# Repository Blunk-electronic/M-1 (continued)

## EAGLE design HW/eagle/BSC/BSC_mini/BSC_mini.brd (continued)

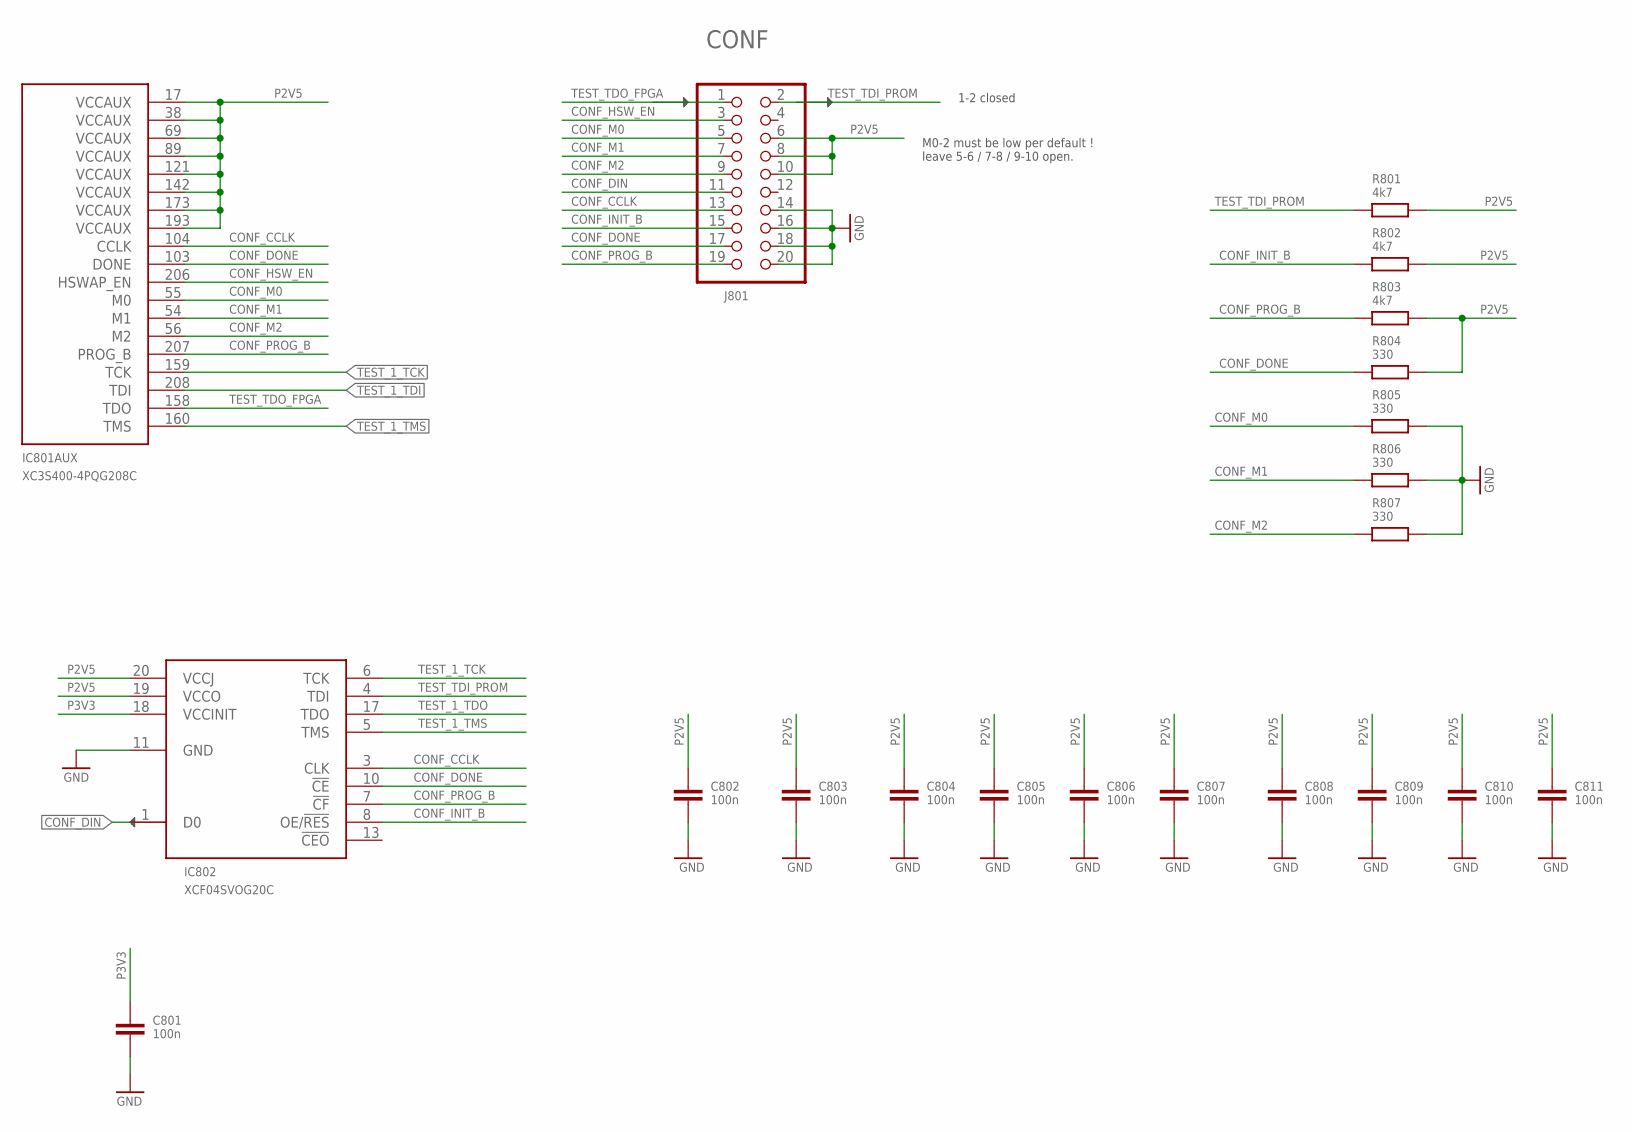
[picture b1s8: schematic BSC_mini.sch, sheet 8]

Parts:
C801, C802, C803, C804, C805, C806, C807, C808, C809, C810, C811: 100n; S_0805; PART_CODE_BEL C_PAC_S_0805_VAL_100n
IC801: XC3S400-4PQG208C; S_PQ208
IC802: XCF04SVOG20C; S_TSSOP20
J801: JUMPER_2X10-T-VERTICAL; T_MALE_2X10_VERTICAL_GRID_2.54MM; PART_CODE_BEL J_PAC_T_MALE_2X10_VERTICAL_PITCH_2mm54
R801, R802, R803: 4k7; S_0805; PART_CODE_BEL R_PAC_S_0805_VAL_4k7
R804, R805, R806, R807: 330; S_0805; PART_CODE_BEL R_PAC_S_0805_VAL_330

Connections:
CONF_CCLK: IC801.104 (CCLK), IC802.3 (CLK), J801.13
CONF_DIN: IC802.1 (D0), J801.11; also elsewhere on the board
CONF_DONE: IC801.103 (DONE), IC802.10 (!CE), J801.17, R804.1
CONF_HSW_EN: IC801.206 (HSWAP_EN), J801.3
CONF_INIT_B: IC802.8 (OE/!RES), J801.15, R802.1; also elsewhere on the board
CONF_M0: IC801.55 (M0), J801.5, R805.1
CONF_M1: IC801.54 (M1), J801.7, R806.1
CONF_M2: IC801.56 (M2), J801.9, R807.1
CONF_PROG_B: IC801.207 (PROG_B), IC802.7 (!CF), J801.19, R803.1
GND: C801.2, C802.2, C803.2, C804.2, C805.2, C806.2, C807.2, C808.2, C809.2, C810.2, C811.2, IC802.11 (GND), J801.14, J801.16, J801.18, J801.20, R805.2, R806.2, R807.2; also elsewhere on the board
P2V5: C802.1, C803.1, C804.1, C805.1, C806.1, C807.1, C808.1, C809.1, C810.1, C811.1, IC801.17 (VCCAUX), IC801.38 (VCCAUX), IC801.69 (VCCAUX), IC801.89 (VCCAUX), IC801.121 (VCCAUX), IC801.142 (VCCAUX), IC801.173 (VCCAUX), IC801.193 (VCCAUX), IC802.19 (VCCO), IC802.20 (VCCJ), J801.6, J801.8, J801.10, R801.2, R802.2, R803.2, R804.2; also elsewhere on the board
P3V3: C801.1, IC802.18 (VCCINIT); also elsewhere on the board
TEST_1_TCK: IC801.159 (TCK), IC802.6 (TCK); also elsewhere on the board
TEST_1_TDI: IC801.208 (TDI); also elsewhere on the board
TEST_1_TDO: IC802.17 (TDO); also elsewhere on the board
TEST_1_TMS: IC801.160 (TMS), IC802.5 (TMS); also elsewhere on the board
TEST_TDI_PROM: IC802.4 (TDI), J801.2, R801.1
TEST_TDO_FPGA: IC801.158 (TDO), J801.1

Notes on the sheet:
M0-2 must be low per default ! leave 5-6 / 7-8 / 9-10 open.
1-2 closed

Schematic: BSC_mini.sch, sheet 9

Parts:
IC801: XC3S400-4PQG208C; S_PQ208

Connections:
CLK_MASTER: IC801.181 (IO_L32N_1/GCLK5); also elsewhere on the board
CLK_SLOW: IC801.154 (IO/VREF_2); also elsewhere on the board
DEBUG_4: IC801.149 (IO_L20N_2); also elsewhere on the board
DEBUG_5: IC801.150 (IO_L19P_2); also elsewhere on the board
DEBUG_6: IC801.152 (IO_L19N_2); also elsewhere on the board
MEM_A0: IC801.122 (IO_L23P_3/VREF_3); also elsewhere on the board
MEM_A1: IC801.123 (IO_L23N_3); also elsewhere on the board
MEM_A2: IC801.124 (IO_L24P_3); also elsewhere on the board
MEM_A3: IC801.125 (IO_L24N_3); also elsewhere on the board
MEM_A4: IC801.126 (IO_L39P_3); also elsewhere on the board
MEM_A5: IC801.128 (IO_L39N_3); also elsewhere on the board
MEM_A6: IC801.130 (IO_L40P_3); also elsewhere on the board
MEM_A7: IC801.131 (IO_L40N_3/VREF_3); also elsewhere on the board
MEM_A8: IC801.132 (IO_L40P_2/VREF_2); also elsewhere on the board
MEM_A9: IC801.133 (IO_L40N_2); also elsewhere on the board
MEM_A10: IC801.135 (IO_L39P_2); also elsewhere on the board
MEM_A11: IC801.137 (IO_L39N_2); also elsewhere on the board
MEM_A12: IC801.138 (IO_L24P_2); also elsewhere on the board
MEM_A13: IC801.139 (IO_L24N_2); also elsewhere on the board
MEM_A14: IC801.140 (IO_L23P_2); also elsewhere on the board
MEM_A15: IC801.141 (IO_L23N_2/VREF_2); also elsewhere on the board
MEM_A16: IC801.143 (IO_L22P_2); also elsewhere on the board
MEM_A17: IC801.144 (IO_L22N_2); also elsewhere on the board
MEM_A18: IC801.146 (IO_L21P_2); also elsewhere on the board
MEM_D0: IC801.106 (IO_L01P_3/VRN_3); also elsewhere on the board
MEM_D1: IC801.107 (IO_L01N_3/VRP_3); also elsewhere on the board
MEM_D2: IC801.108 (IO_L17P_3/VREF_3); also elsewhere on the board
MEM_D3: IC801.109 (IO_L17N_3); also elsewhere on the board
MEM_D4: IC801.111 (IO_L19P_3); also elsewhere on the board
MEM_D5: IC801.113 (IO_L19N_3); also elsewhere on the board
MEM_D6: IC801.114 (IO_L20P_3); also elsewhere on the board
MEM_D7: IC801.115 (IO_L20N_3); also elsewhere on the board
P3V3: IC801.110 (VCCO_3), IC801.127 (VCCO_3), IC801.136 (VCCO_2), IC801.153 (VCCO_2), IC801.164 (VCCO_1), IC801.177 (VCCO_1), IC801.188 (VCCO_0), IC801.201 (VCCO_0); also elsewhere on the board
RAM_IN_CS_N: IC801.117 (IO_L21N_3); also elsewhere on the board
RAM_OE_N: IC801.120 (IO_L22N_3); also elsewhere on the board
RAM_OUT_CS_1_N: IC801.116 (IO_L21P_3); also elsewhere on the board
RAM_OUT_CS_2_N: IC801.147 (IO_L21N_2); also elsewhere on the board
RAM_WE_N: IC801.119 (IO_L22P_3); also elsewhere on the board
ROM_CS_N: IC801.148 (IO_L20P_2); also elsewhere on the board
ST_1_OUT: IC801.166 (IO_L10N_1/VREF_1); also elsewhere on the board
ST_2_OUT: IC801.165 (IO_L10P_1); also elsewhere on the board
SYS_RESET_N: IC801.182 (IO); also elsewhere on the board
UART_CTS: IC801.199 (IO_L25N_0); also elsewhere on the board
UART_RTS: IC801.198 (IO_L25P_0); also elsewhere on the board
UART_RXD: IC801.203 (IO_L01P_0/VRN_0); also elsewhere on the board
UART_TXD: IC801.200 (IO/VREF_0); also elsewhere on the board

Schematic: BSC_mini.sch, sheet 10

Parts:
IC801: XC3S400-4PQG208C; S_PQ208
TP1001, TP1002, TP1003: TEST_POINT_T_SMALL; T_TEST_POINT_SMALL

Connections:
ACL_OUT: IC801.2 (IO_L01P_7/VRN_7); also elsewhere on the board
CONF_DIN: IC801.92 (IO_L27N_4/DIN/D0); also elsewhere on the board
CONF_DOUT: IC801.81 (IO_L31P_4/DOUT/BUSY), TP1002.1
CONF_INIT_B: IC801.83 (IO_L31N_4/INIT_B); also elsewhere on the board
CTRL_IN_START_N: IC801.35 (IO_L24N_6/VREF_6); also elsewhere on the board
CTRL_IN_STOP_N: IC801.34 (IO_L24P_6); also elsewhere on the board
CTRL_OUT_FAIL: IC801.58 (IO_L01N_5/RDWR_B); also elsewhere on the board
CTRL_OUT_PASS: IC801.57 (IO_L01P_5/CS_B); also elsewhere on the board
DBG_3: IC801.43 (IO_L21N_6); also elsewhere on the board
DBG_4: IC801.96 (IO/VREF_4); also elsewhere on the board
DBG_5: IC801.40 (IO_L22N_6); also elsewhere on the board
DBG_6: IC801.39 (IO_L22P_6); also elsewhere on the board
DBG_80: IC801.80 (IO_L32N_4/GCLK1), TP1003.1
DBG_81: IC801.97 (IO), TP1001.1
DCL_OUT: IC801.3 (IO_L01N_7/VRP_7); also elsewhere on the board
DEBUG_0: IC801.61 (IO_L10P_5/VRN_5); also elsewhere on the board
DEBUG_1: IC801.33 (IO_L39N_6); also elsewhere on the board
DEBUG_2: IC801.44 (IO_L20P_6); also elsewhere on the board
DEBUG_3: IC801.37 (IO_L23N_6); also elsewhere on the board
I2C_SCL: IC801.51 (IO_L01P_6/VRN_6); also elsewhere on the board
I2C_SDA: IC801.52 (IO_L01N_6/VRP_6); also elsewhere on the board
OBI_1: IC801.36 (IO_L23P_6); also elsewhere on the board
OBI_2: IC801.4 (IO_L16P_7/VREF_7); also elsewhere on the board
OBI_3: IC801.10 (IO_L20P_7); also elsewhere on the board
OBI_4: IC801.11 (IO_L20N_7); also elsewhere on the board
OBI_5: IC801.12 (IO_L21P_7); also elsewhere on the board
OBI_6: IC801.29 (IO_L40N_6); also elsewhere on the board
OBI_7: IC801.50 (IO/VREF_6); also elsewhere on the board
OBI_8: IC801.48 (IO_L19N_6); also elsewhere on the board
OBI_9: IC801.46 (IO_L19P_6); also elsewhere on the board
OBI_10: IC801.45 (IO_L20N_6); also elsewhere on the board
P2V5: IC801.84 (VCCO_4), IC801.98 (VCCO_4); also elsewhere on the board
P3V3: IC801.6 (VCCO_7), IC801.23 (VCCO_7), IC801.32 (VCCO_6), IC801.49 (VCCO_6), IC801.60 (VCCO_5), IC801.73 (VCCO_5); also elsewhere on the board
SP_1_FAIL_FPGA: IC801.63 (IO); also elsewhere on the board
SP_1_TCK_FPGA: IC801.76 (IO_L32P_5/GCLK2); also elsewhere on the board
SP_1_TDI_FPGA: IC801.78 (IO/VREF_5); also elsewhere on the board
SP_1_TDO_FPGA: IC801.68 (IO_L28N_5/D6); also elsewhere on the board
SP_1_TMS_FPGA: IC801.74 (IO_L31N_5/D4); also elsewhere on the board
SP_1_TRST_FPGA: IC801.65 (IO_L27N_5/VREF_5); also elsewhere on the board
SP_2_FAIL_FPGA: IC801.62 (IO_L10N_5/VRP_5); also elsewhere on the board
SP_2_TCK_FPGA: IC801.77 (IO_L32N_5/GCLK3); also elsewhere on the board
SP_2_TDI_FPGA: IC801.71 (IO); also elsewhere on the board
SP_2_TDO_FPGA: IC801.67 (IO_L28P_5/D7); also elsewhere on the board
SP_2_TMS_FPGA: IC801.72 (IO_L31P_5/D5); also elsewhere on the board
SP_2_TRST_FPGA: IC801.64 (IO_L27P_5); also elsewhere on the board

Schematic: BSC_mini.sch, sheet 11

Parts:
C1101, C1102, C1103, C1104, C1105, C1106, C1107, C1108, C1109, C1110, C1111, C1112, C1113, C1114, C1115, C1116, C1117, C1118, C1119, C1120: 100n; S_0805; PART_CODE_BEL C_PAC_S_0805_VAL_100n
IC801: XC3S400-4PQG208C; S_PQ208
IC1101: 50MHz; S_XO91; PART_CODE_BEL IC_PAC_S_XO91_7x5mm_VAL_50MHz
TP1101: TEST_POINT_T_SMALL; T_TEST_POINT_SMALL

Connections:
CLK_MASTER: IC1101.3 (FO), TP1101.1; also elsewhere on the board
GND: C1101.2, C1102.2, C1103.2, C1104.2, C1105.2, C1106.2, C1107.2, C1108.2, C1109.2, C1110.2, C1111.2, C1112.2, C1113.2, C1114.2, C1115.2, C1116.2, C1117.2, C1118.2, C1119.2, C1120.2, IC801.1 (GND), IC801.8 (GND), IC801.14 (GND), IC801.25 (GND), IC801.30 (GND), IC801.41 (GND), IC801.47 (GND), IC801.53 (GND), IC801.59 (GND), IC801.66 (GND), IC801.75 (GND), IC801.82 (GND), IC801.91 (GND), IC801.99 (GND), IC801.105 (GND), IC801.112 (GND), IC801.118 (GND), IC801.129 (GND), IC801.134 (GND), IC801.145 (GND), IC801.151 (GND), IC801.157 (GND), IC801.163 (GND), IC801.170 (GND), IC801.179 (GND), IC801.186 (GND), IC801.195 (GND), IC801.202 (GND), IC1101.2 (GND); also elsewhere on the board
P1V2: C1117.1, C1118.1, C1119.1, C1120.1, IC801.70 (VCCINT), IC801.88 (VCCINT), IC801.174 (VCCINT), IC801.192 (VCCINT); also elsewhere on the board
P2V5: C1114.1; also elsewhere on the board
P3V3: C1101.1, C1102.1, C1103.1, C1104.1, C1105.1, C1106.1, C1107.1, C1108.1, C1109.1, C1110.1, C1111.1, C1112.1, C1113.1, C1115.1, C1116.1, IC1101.4 (VCC); also elsewhere on the board

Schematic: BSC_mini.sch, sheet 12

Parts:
IC1201: XC2C384-10TQG144C; S_TQFP144; PART_CODE_BEL IC_PAC_S_TQFP144_VAL_XC2C384-10TQG144C
J1201: JUMPER_1X2-T-VERTICAL_GRID_2.54MM; T_MALE_2X1_VERTICAL_PITCH_2MM54
R1201, R1202: 330; S_0805; PART_CODE_BEL R_PAC_S_0805_VAL_330
RN1201: 10k; S_1206_4X; PART_CODE_BEL RN_PAC_S_1206_4X_VAL_10k
X1201, X1202: MALE_2X5-T-VERTICAL_2MM54; T_MALE_2X5_VERTICAL_PITCH_2MM54

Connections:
GND: R1201.1, R1202.1, X1201.2, X1201.4, X1201.6, X1201.8, X1202.2, X1202.4, X1202.6, X1202.8; also elsewhere on the board
P3V3: J1201.1; also elsewhere on the board
TEST_2_TCK: IC1201.67 (TCK), R1201.2, X1201.1, X1202.1
TEST_2_TDI: IC1201.63 (TDI), RN1201.2 (1), X1201.7, X1202.7
TEST_2_TDO: IC1201.122 (TDO), RN1201.3 (1), X1201.5, X1202.5
TEST_2_TMS: IC1201.65 (TMS), R1202.2, X1201.3, X1202.3
TEST_2_VREF: J1201.2, RN1201.6 (2), RN1201.7 (2), X1201.10, X1202.10

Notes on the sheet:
NOTE: close for in-system-programming

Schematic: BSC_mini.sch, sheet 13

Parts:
C1301, C1302: 100n; S_0805; PART_CODE_BEL C_PAC_S_0805_VAL_100n
IC1301, IC1302: MAX517ACSA+; S_SO8; PART_CODE_BEL IC_PAC_S_SO8_VAL_MAX517ACSA+
R1301, R1302: 330; S_0805; PART_CODE_BEL R_PAC_S_0805_VAL_330

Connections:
GND: C1301.2, C1302.2, IC1301.2 (GND), IC1301.5 (A1), IC1301.6 (A0), IC1302.2 (GND), IC1302.5 (A1); also elsewhere on the board
I2C_SCL: IC1301.3 (SCL), IC1302.3 (SCL), R1301.1; also elsewhere on the board
I2C_SDA: IC1301.4 (SDA), IC1302.4 (SDA), R1302.1; also elsewhere on the board
P3V3: IC1301.8 (VREF0), IC1302.8 (VREF0), R1301.2, R1302.2; also elsewhere on the board
P5V: C1301.1, C1302.1, IC1301.7 (VCC), IC1302.6 (A0), IC1302.7 (VCC); also elsewhere on the board
SP_1_TDI_VREF: IC1301.1 (OUT0); also elsewhere on the board
SP_2_TDI_VREF: IC1302.1 (OUT0); also elsewhere on the board

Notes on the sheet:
I²C write addr 58h
I²C write addr 5Ah

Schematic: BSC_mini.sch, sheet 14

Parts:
C1401: 100n; S_0805; PART_CODE_BEL C_PAC_S_0805_VAL_100n
D1401, D1402: BAT54S; S_SOT23; PART_CODE_BEL D_PAC_S_SOT23_VAL_BAT54S
IC1401: MAX962ESA+; S_SO8; PART_CODE_BEL IC_PAC_S_SO8_VAL_MAX962ESA+
R1401, R1403: 8k2; S_0805; PART_CODE_BEL R_PAC_S_0805_VAL_8k2
R1402, R1404: 2k7; S_0805; PART_CODE_BEL R_PAC_S_0805_VAL_2k7
TP1401, TP1402, TP1403, TP1404, TP1405, TP1406: TEST_POINT_T_SMALL; T_TEST_POINT_SMALL

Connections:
GND: C1401.1, D1401.1 (A2), D1402.1 (A2), IC1401.5 (V-), R1402.1, R1404.1; also elsewhere on the board
P3V3: C1401.2, D1401.2 (K1), D1402.2 (K1), IC1401.8 (V+), R1401.2, R1403.2; also elsewhere on the board
SP_1_TDI: D1401.3 (A1K2), IC1401.3 (+IN), TP1401.1; also elsewhere on the board
SP_1_TDI_COMP: IC1401.6 (OUT), TP1405.1; also elsewhere on the board
SP_1_TDI_VREF: IC1401.4 (-IN), R1401.1, R1402.2, TP1402.1; also elsewhere on the board
SP_2_TDI: D1402.3 (A1K2), IC1401.1 (+IN), TP1403.1; also elsewhere on the board
SP_2_TDI_COMP: IC1401.7 (OUT), TP1406.1; also elsewhere on the board
SP_2_TDI_VREF: IC1401.2 (-IN), R1403.1, R1404.2, TP1404.1; also elsewhere on the board

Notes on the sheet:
fixed reference voltage for comparators NOT FITTED
0.82V

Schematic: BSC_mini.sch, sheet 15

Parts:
IC1201: XC2C384-10TQG144C; S_TQFP144; PART_CODE_BEL IC_PAC_S_TQFP144_VAL_XC2C384-10TQG144C

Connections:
DEBUG_10: IC1201.143 (B2_FB1_MC3(GSR)); also elsewhere on the board
DEBUG_11: IC1201.142 (B2_FB1_MC4); also elsewhere on the board
DEBUG_12: IC1201.34 (B1_FB7_MC4); also elsewhere on the board
DEBUG_13: IC1201.33 (B1_FB7_MC5); also elsewhere on the board
DEBUG_14: IC1201.38 (B1_FB8_MC2(GCK2)); also elsewhere on the board
DEBUG_15: IC1201.39 (B1_FB8_MC5(DGE)); also elsewhere on the board
DEBUG_16: IC1201.40 (B1_FB8_MC13); also elsewhere on the board
DEBUG_17: IC1201.41 (B1_FB8_MC14); also elsewhere on the board
DEBUG_18: IC1201.42 (B1_FB8_MC15); also elsewhere on the board
DISP_1_SEG_A: IC1201.7 (B2_FB2_MC16); also elsewhere on the board
DISP_1_SEG_B: IC1201.6 (B2_FB2_MC15(GTS1)); also elsewhere on the board
DISP_1_SEG_C: IC1201.4 (B2_FB2_MC4); also elsewhere on the board
DISP_1_SEG_D: IC1201.2 (B2_FB2_MC1(GTS2)); also elsewhere on the board
DISP_1_SEG_E: IC1201.3 (B2_FB2_MC3(GTS3)); also elsewhere on the board
DISP_1_SEG_F: IC1201.5 (B2_FB2_MC5(GTS0)); also elsewhere on the board
DISP_1_SEG_G: IC1201.23 (B1_FB11_MC2); also elsewhere on the board
DISP_1_SEG_H: IC1201.25 (B1_FB9_MC16); also elsewhere on the board
DISP_2_SEG_A: IC1201.26 (B1_FB9_MC15); also elsewhere on the board
DISP_2_SEG_B: IC1201.28 (B1_FB9_MC2); also elsewhere on the board
DISP_2_SEG_C: IC1201.24 (B1_FB11_MC1); also elsewhere on the board
DISP_2_SEG_D: IC1201.50 (B1_FB10_MC16); also elsewhere on the board
DISP_2_SEG_E: IC1201.49 (B1_FB10_MC15); also elsewhere on the board
DISP_2_SEG_F: IC1201.44 (B1_FB10_MC1); also elsewhere on the board
DISP_2_SEG_G: IC1201.46 (B1_FB10_MC4); also elsewhere on the board
DISP_2_SEG_H: IC1201.48 (B1_FB10_MC14); also elsewhere on the board
I2C_SCL: IC1201.32 (B1_FB7_MC12(GCK1)); also elsewhere on the board
I2C_SDA: IC1201.31 (B1_FB7_MC14); also elsewhere on the board
OBI_1: IC1201.139 (B2_FB1_MC13); also elsewhere on the board
OBI_2: IC1201.52 (B1_FB12_MC2); also elsewhere on the board
OBI_3: IC1201.51 (B1_FB12_MC1); also elsewhere on the board
OBI_4: IC1201.45 (B1_FB10_MC2); also elsewhere on the board
OBI_5: IC1201.43 (B1_FB8_MC16); also elsewhere on the board
OBI_6: IC1201.140 (B2_FB1_MC12); also elsewhere on the board
OBI_7: IC1201.22 (B1_FB11_MC3); also elsewhere on the board
OBI_8: IC1201.21 (B1_FB11_MC4); also elsewhere on the board
OBI_9: IC1201.20 (B1_FB11_MC5); also elsewhere on the board
OBI_10: IC1201.19 (B1_FB11_MC12); also elsewhere on the board
SP_1_DIO_1_ADJ: IC1201.102 (B4_FB16_MC3); also elsewhere on the board
SP_1_DIO_1_P3V3: IC1201.135 (B2_FB3_MC12); also elsewhere on the board
SP_1_DIO_2_ADJ: IC1201.105 (B4_FB14_MC5); also elsewhere on the board
SP_1_DIO_2_P3V3: IC1201.136 (B2_FB3_MC5); also elsewhere on the board
SP_1_TCK: IC1201.104 (B4_FB14_MC13); also elsewhere on the board
SP_1_TCK_FPGA: IC1201.9 (B2_FB4_MC1); also elsewhere on the board
SP_1_TDI_COMP: IC1201.137 (B2_FB3_MC4); also elsewhere on the board
SP_1_TDI_FPGA: IC1201.17 (B2_FB6_MC14); also elsewhere on the board
SP_1_TDO: IC1201.107 (B4_FB14_MC3); also elsewhere on the board
SP_1_TDO_FPGA: IC1201.11 (B2_FB4_MC3); also elsewhere on the board
SP_1_TMS: IC1201.103 (B4_FB16_MC1); also elsewhere on the board
SP_1_TMS_FPGA: IC1201.10 (B2_FB4_MC2); also elsewhere on the board
SP_1_TRST_FPGA: IC1201.12 (B2_FB4_MC4); also elsewhere on the board
SP_1_TRST_N: IC1201.106 (B4_FB14_MC4); also elsewhere on the board
SP_1_VCC_P1V5_SET: IC1201.134 (B2_FB3_MC16); also elsewhere on the board
SP_1_VCC_P1V8_SET: IC1201.133 (B2_FB5_MC2); also elsewhere on the board
SP_1_VCC_P2V5_SET: IC1201.132 (B2_FB5_MC3); also elsewhere on the board
SP_2_DIO_1_ADJ: IC1201.87 (B3_FB23_MC5); also elsewhere on the board
SP_2_DIO_1_P3V3: IC1201.53 (B1_FB12_MC3); also elsewhere on the board
SP_2_DIO_2_ADJ: IC1201.85 (B3_FB23_MC3); also elsewhere on the board
SP_2_DIO_2_P3V3: IC1201.54 (B1_FB12_MC5); also elsewhere on the board
SP_2_TCK: IC1201.92 (B3_FB23_MC14); also elsewhere on the board
SP_2_TCK_FPGA: IC1201.13 (B2_FB6_MC2); also elsewhere on the board
SP_2_TDI_COMP: IC1201.138 (B2_FB3_MC3); also elsewhere on the board
SP_2_TDI_FPGA: IC1201.18 (B2_FB6_MC16); also elsewhere on the board
SP_2_TDO: IC1201.88 (B3_FB23_MC12); also elsewhere on the board
SP_2_TDO_FPGA: IC1201.15 (B2_FB6_MC4); also elsewhere on the board
SP_2_TMS: IC1201.91 (B3_FB23_MC13); also elsewhere on the board
SP_2_TMS_FPGA: IC1201.14 (B2_FB6_MC3); also elsewhere on the board
SP_2_TRST_FPGA: IC1201.16 (B2_FB6_MC13); also elsewhere on the board
SP_2_TRST_N: IC1201.86 (B3_FB23_MC4); also elsewhere on the board
SP_2_VCC_P1V5_SET: IC1201.131 (B2_FB5_MC13); also elsewhere on the board
SP_2_VCC_P1V8_SET: IC1201.130 (B2_FB5_MC15); also elsewhere on the board
SP_2_VCC_P2V5_SET: IC1201.129 (B2_FB5_MC16); also elsewhere on the board
SYS_RESET_N: IC1201.35 (B1_FB7_MC1(CDRST)); also elsewhere on the board

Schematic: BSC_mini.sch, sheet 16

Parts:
C1601, C1602, C1603, C1604, C1605, C1606, C1607, C1608, C1609, C1610, C1611: 100n; S_0805; PART_CODE_BEL C_PAC_S_0805_VAL_100n
IC1201: XC2C384-10TQG144C; S_TQFP144; PART_CODE_BEL IC_PAC_S_TQFP144_VAL_XC2C384-10TQG144C

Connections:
GND: C1601.2, C1602.2, C1603.2, C1604.2, C1605.2, C1606.2, C1607.2, C1608.2, C1609.2, C1610.2, C1611.2, IC1201.29 (GND), IC1201.36 (GND), IC1201.47 (GND), IC1201.62 (GND), IC1201.72 (GND), IC1201.89 (GND), IC1201.90 (GND), IC1201.99 (GND), IC1201.108 (GND), IC1201.123 (GND), IC1201.144 (GND); also elsewhere on the board
P1V8: C1603.1, C1606.1, C1609.1, IC1201.1 (VCC), IC1201.37 (VCC), IC1201.84 (VCC); also elsewhere on the board
P3V3: C1602.1, C1605.1, C1608.1, C1611.1, IC1201.8 (VAUX), IC1201.27 (VCC_IO), IC1201.55 (VCC_IO), IC1201.141 (VCC_IO); also elsewhere on the board
SP_1_VCC: C1601.1, C1604.1, IC1201.109 (VCC_IO), IC1201.127 (VCC_IO); also elsewhere on the board
SP_2_VCC: C1607.1, C1610.1, IC1201.73 (VCC_IO), IC1201.93 (VCC_IO); also elsewhere on the board

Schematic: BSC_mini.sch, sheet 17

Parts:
LED1701, LED1702: green; S_0805; PART_CODE_BEL LED_PAC_S_0805_VAL_green
LED1703, LED1704: yellow; S_0805; PART_CODE_BEL LED_PAC_S_0805_VAL_yellow
LED1705, LED1708: blue; S_0805; PART_CODE_BEL LED_PAC_S_0805_VAL_blue
LED1706, LED1707: red; S_0805; PART_CODE_BEL LED_PAC_S_0805_VAL_red
R1701, R1702: 160; S_0805; PART_CODE_BEL R_PAC_S_0805_VAL_160
R1703, R1704: 470; S_0805; PART_CODE_BEL R_PAC_S_0805_VAL_470
R1705, R1708: 330; S_0805; PART_CODE_BEL R_PAC_S_0805_VAL_330
R1706, R1707: 750; S_0805; PART_CODE_BEL R_PAC_S_0805_VAL_750
TP1701: TEST_POINT_T_SMALL; T_TEST_POINT_SMALL
X1701, X1702: MALE_2X20-T-VERTICAL; T_MALE_2X20_VERTICAL_GRID_2.54MM

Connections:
ACL_RC: X1702.40; also elsewhere on the board
CLK_SLOW: X1701.16; also elsewhere on the board
CTRL_IN_START: X1701.34; also elsewhere on the board
CTRL_IN_STOP: X1701.36; also elsewhere on the board
CTRL_OUT_FAIL: X1701.32; also elsewhere on the board
CTRL_OUT_PASS: X1701.30; also elsewhere on the board
DBG_3: X1702.8; also elsewhere on the board
DBG_4: X1702.10; also elsewhere on the board
DBG_5: X1702.12; also elsewhere on the board
DBG_6: X1702.14; also elsewhere on the board
DBG_10_LED: LED1702.C, R1702.2
DBG_11_LED: LED1704.C, R1704.2
DBG_12_LED: LED1706.C, R1706.2
DBG_13_LED: LED1708.C, R1708.2
DEBUG_0: R1701.1, X1702.2; also elsewhere on the board
DEBUG_1: R1703.1, X1702.4; also elsewhere on the board
DEBUG_2: R1705.1, X1702.6; also elsewhere on the board
DEBUG_3: X1702.16; also elsewhere on the board
DEBUG_10: X1702.32; also elsewhere on the board
DEBUG_11: TP1701.1, X1701.14; also elsewhere on the board
DEBUG_12: X1702.28; also elsewhere on the board
DEBUG_13: X1702.30; also elsewhere on the board
DEBUG_14: X1702.26; also elsewhere on the board
DEBUG_15: R1708.1, X1702.24; also elsewhere on the board
DEBUG_16: R1706.1, X1702.22; also elsewhere on the board
DEBUG_17: R1704.1, X1702.20; also elsewhere on the board
DEBUG_18: R1702.1, X1702.18; also elsewhere on the board
DGB_0_LED: LED1701.C, R1701.2
DGB_1_LED: LED1703.C, R1703.2
DGB_2_LED: LED1705.C, R1705.2
GND: X1701.1, X1701.3, X1701.5, X1701.7, X1701.9, X1701.11, X1701.13, X1701.15, X1701.17, X1701.19, X1701.21, X1701.23, X1701.25, X1701.27, X1701.29, X1701.31, X1701.33, X1701.35, X1701.37, X1701.39, X1702.1, X1702.3, X1702.5, X1702.7, X1702.9, X1702.11, X1702.13, X1702.15, X1702.17, X1702.19, X1702.21, X1702.23, X1702.25, X1702.27, X1702.29, X1702.31, X1702.33, X1702.35, X1702.37, X1702.39; also elsewhere on the board
I2C_SCL: X1701.28; also elsewhere on the board
I2C_SDA: X1701.26; also elsewhere on the board
P3V3: LED1701.A, LED1702.A, LED1703.A, LED1704.A, LED1705.A, LED1706.A, LED1707.A, LED1708.A; also elsewhere on the board
RAM_WE_N: X1702.34; also elsewhere on the board
RESET_SWITCH_N: X1701.40; also elsewhere on the board
SP_1_TDI_VREF: X1701.2; also elsewhere on the board
SP_2_TDI_VREF: X1701.4; also elsewhere on the board
ST_1_IN: X1701.18; also elsewhere on the board
ST_1_OUT: X1701.22; also elsewhere on the board
ST_2_IN: X1701.20; also elsewhere on the board
ST_2_OUT: X1701.24; also elsewhere on the board
SYS_RESET_LED: LED1707.C, R1707.2
SYS_RESET_N: R1707.1, X1701.38; also elsewhere on the board

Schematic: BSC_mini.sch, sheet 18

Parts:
C1801, C1802, C1803: 100n; S_0805; PART_CODE_BEL C_PAC_S_0805_VAL_100n
FD1801, FD1802: FIDUCIAL_CROSSHAIR; CROSSHAIR
H1801, H1802, H1803, H1804: HOLE_4.1_PAD; 4.1_PAD
IC1801: 4093N; T_NDIP14
LED1801: green; S_0805; PART_CODE_BEL LED_PAC_S_0805_VAL_green
LED1802: red; S_0805; PART_CODE_BEL LED_PAC_S_0805_VAL_red
R1801: 160; S_0805; PART_CODE_BEL R_PAC_S_0805_VAL_160
R1802: 750; S_0805; PART_CODE_BEL R_PAC_S_0805_VAL_750
R1803, R1804: 1M; S_0805; PART_CODE_BEL R_PAC_S_0805_VAL_1M
RN1801: 100; T_SIL8; PART_CODE_BEL RN_PAC_T_SIL8_VAL_100
S1801, S1802: PUSH_BUTTON_T_6X6MM; T_PUSH_BUTTON_6X6; PART_CODE_BEL S_PAC_T_PUSH_BUTTON_6X6mm
TP1801, TP1802: TEST_POINT_T_SMALL; T_TEST_POINT_SMALL

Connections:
CTRL_IN_START: C1802.1, IC1801.8 (I0), IC1801.9 (I1), R1804.1, S1802.2 (B1), S1802.4 (B1); also elsewhere on the board
CTRL_IN_START_N: IC1801.10 (O); also elsewhere on the board
CTRL_IN_STOP: C1801.1, IC1801.12 (I0), IC1801.13 (I1), R1803.1, S1801.2 (B1), S1801.4 (B1); also elsewhere on the board
CTRL_IN_STOP_N: IC1801.11 (O); also elsewhere on the board
CTRL_OUT_FAIL: R1802.1; also elsewhere on the board
CTRL_OUT_FAIL_LED: LED1802.A, R1802.2
CTRL_OUT_PASS: R1801.1; also elsewhere on the board
CTRL_OUT_PASS_LED: LED1801.A, R1801.2
GND: C1803.2, H1801.H1, H1802.H1, H1803.H1, H1804.H1, IC1801.7 (GND), LED1801.C, LED1802.C, R1803.2, R1804.2, RN1801.1, RN1801.3 (1), RN1801.5 (1), RN1801.7 (1); also elsewhere on the board
P3V3: C1801.2, C1802.2, C1803.1, IC1801.14 (VCC), S1801.1 (A1), S1801.3 (A1), S1802.1 (A1), S1802.3 (A1); also elsewhere on the board
RSV_ST_IN_1: IC1801.1 (I0), RN1801.2
RSV_ST_IN_2: IC1801.2 (I1), RN1801.4 (2)
RSV_ST_IN_3: IC1801.5 (I0), RN1801.6 (2)
RSV_ST_IN_4: IC1801.6 (I1), RN1801.8 (2)
RSV_ST_OUT_1: IC1801.3 (O), TP1801.1
RSV_ST_OUT_2: IC1801.4 (O), TP1802.1

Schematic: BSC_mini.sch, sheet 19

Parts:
DIS1901: VQE14; T_VQEXX_2DIGIT; PART_CODE_BEL DIS_PAC_T_VQExx_2DIGIT_VAL_VQE14
J1901, J1902, J1903, J1904: SOLDER_JUMPER-N; S_SOLDER_JUMPER_NARROW
LED1901: yellow; S_0805; PART_CODE_BEL LED_PAC_S_0805_VAL_yellow
LED1902: blue; S_0805; PART_CODE_BEL LED_PAC_S_0805_VAL_blue
R1901, R1903: 100k; S_0805; PART_CODE_BEL R_PAC_S_0805_VAL_100k
R1902: 470; S_0805; PART_CODE_BEL R_PAC_S_0805_VAL_470
R1904: 330; S_0805; PART_CODE_BEL R_PAC_S_0805_VAL_330
RN1901, RN1902, RN1903, RN1904: 100; T_SIL8; PART_CODE_BEL RN_PAC_T_SIL8_VAL_100
T1901, T1902: DMG3420U; S_SOT23; PART_CODE_BEL T_PAC_S_SOT23_VAL_DMG3420U
TP1901, TP1902, TP1903, TP1904: TEST_POINT_T_SMALL; T_TEST_POINT_SMALL

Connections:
DISP_1_COM: DIS1901.4 (COM1), J1901.2, J1902.2
DISP_1_SEG_A: RN1901.1; also elsewhere on the board
DISP_1_SEG_A_R: DIS1901.16 (A1), RN1901.2
DISP_1_SEG_B: RN1901.3 (1); also elsewhere on the board
DISP_1_SEG_B_R: DIS1901.14 (B1), RN1901.4 (2)
DISP_1_SEG_C: RN1901.5 (1); also elsewhere on the board
DISP_1_SEG_C_R: DIS1901.1 (C1), RN1901.6 (2)
DISP_1_SEG_D: RN1901.7 (1); also elsewhere on the board
DISP_1_SEG_D_R: DIS1901.3 (D1), RN1901.8 (2)
DISP_1_SEG_E: RN1902.1; also elsewhere on the board
DISP_1_SEG_E_R: DIS1901.2 (E1), RN1902.2
DISP_1_SEG_F: RN1902.3 (1); also elsewhere on the board
DISP_1_SEG_F_R: DIS1901.15 (F1), RN1902.4 (2)
DISP_1_SEG_G: RN1902.5 (1); also elsewhere on the board
DISP_1_SEG_G_R: DIS1901.17 (G1), RN1902.6 (2)
DISP_1_SEG_H: RN1902.7 (1); also elsewhere on the board
DISP_1_SEG_H_R: DIS1901.18 (DP1), RN1902.8 (2)
DISP_2_COM: DIS1901.5 (COM2), J1903.1, J1904.1
DISP_2_SEG_A: RN1903.2; also elsewhere on the board
DISP_2_SEG_A_R: DIS1901.11 (A2), RN1903.1
DISP_2_SEG_B: RN1903.4 (2); also elsewhere on the board
DISP_2_SEG_B_R: DIS1901.13 (B2), RN1903.3 (1)
DISP_2_SEG_C: RN1903.6 (2); also elsewhere on the board
DISP_2_SEG_C_R: DIS1901.8 (C2), RN1903.5 (1)
DISP_2_SEG_D: RN1903.8 (2); also elsewhere on the board
DISP_2_SEG_D_R: DIS1901.6 (D2), RN1903.7 (1)
DISP_2_SEG_E: RN1904.2; also elsewhere on the board
DISP_2_SEG_E_R: DIS1901.7 (E2), RN1904.1
DISP_2_SEG_F: RN1904.4 (2); also elsewhere on the board
DISP_2_SEG_F_R: DIS1901.12 (F2), RN1904.3 (1)
DISP_2_SEG_G: RN1904.6 (2); also elsewhere on the board
DISP_2_SEG_G_R: DIS1901.10 (G2), RN1904.5 (1)
DISP_2_SEG_H: RN1904.7 (1); also elsewhere on the board
DISP_2_SEG_H_R: DIS1901.9 (DP2), RN1904.8 (2)
GND: J1902.1, J1904.2, T1901.2 (S), T1902.2 (S); also elsewhere on the board
I2C_SCL: R1901.1; also elsewhere on the board
I2C_SCL_G: R1901.2, T1901.1 (G)
I2C_SCL_LED: LED1901.C, R1902.2
I2C_SCL_TR: R1902.1, T1901.3 (D)
I2C_SDA: R1903.1; also elsewhere on the board
I2C_SDA_G: R1903.2, T1902.1 (G)
I2C_SDA_LED: LED1902.C, R1904.2
I2C_SDA_TR: R1904.1, T1902.3 (D)
OBI_2: TP1904.1; also elsewhere on the board
OBI_3: TP1903.1; also elsewhere on the board
OBI_4: TP1902.1; also elsewhere on the board
OBI_5: TP1901.1; also elsewhere on the board
P3V3: J1901.1, J1903.2, LED1901.A, LED1902.A; also elsewhere on the board

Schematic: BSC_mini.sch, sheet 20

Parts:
C2001: 1u; S_0805; PART_CODE_BEL C_PAC_S_0805_VAL_1u
C2002: 100n; S_0805; PART_CODE_BEL C_PAC_S_0805_VAL_100n
IC2001: 4093N; T_NDIP14
R2001: 1M; S_0805; PART_CODE_BEL R_PAC_S_0805_VAL_1M
TP2001: clk_slow; T_TEST_POINT_SMALL

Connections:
ACL_IN: IC2001.11 (O), R2001.2
ACL_OUT: IC2001.10 (O); also elsewhere on the board
ACL_RC: C2001.1, IC2001.8 (I0), R2001.1, TP2001.1; also elsewhere on the board
DCL_1: IC2001.3 (O), IC2001.5 (I0)
DCL_OUT: IC2001.4 (O); also elsewhere on the board
DEBUG_14: IC2001.1 (I0); also elsewhere on the board
DEBUG_15: IC2001.2 (I1); also elsewhere on the board
DEBUG_16: IC2001.6 (I1); also elsewhere on the board
DEBUG_17: IC2001.9 (I1); also elsewhere on the board
DEBUG_18: IC2001.12 (I0), IC2001.13 (I1); also elsewhere on the board
GND: C2001.2, C2002.2, IC2001.7 (GND); also elsewhere on the board
P3V3: C2002.1, IC2001.14 (VCC); also elsewhere on the board

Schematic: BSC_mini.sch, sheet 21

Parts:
LED2101, LED2102: yellow; S_0805; PART_CODE_BEL LED_PAC_S_0805_VAL_yellow
LED2103, LED2104: blue; S_0805; PART_CODE_BEL LED_PAC_S_0805_VAL_blue
LED2105, LED2106, LED2107, LED2108: green; S_0805; PART_CODE_BEL LED_PAC_S_0805_VAL_green
LED2109, LED2110: red; S_0805; PART_CODE_BEL LED_PAC_S_0805_VAL_red
R2101, R2102, R2105, R2106, R2109, R2110, R2113, R2114, R2117, R2118: 100k; S_0805; PART_CODE_BEL R_PAC_S_0805_VAL_100k
R2103, R2104: 470; S_0805; PART_CODE_BEL R_PAC_S_0805_VAL_470
R2107, R2108: 330; S_0805; PART_CODE_BEL R_PAC_S_0805_VAL_330
R2111, R2112, R2115, R2116: 160; S_0805; PART_CODE_BEL R_PAC_S_0805_VAL_160
R2119, R2120: 750; S_0805; PART_CODE_BEL R_PAC_S_0805_VAL_750
T2101, T2102, T2103, T2104, T2105, T2106, T2107, T2108, T2109, T2110: DMG3420U; S_SOT23; PART_CODE_BEL T_PAC_S_SOT23_VAL_DMG3420U

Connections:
GND: T2101.2 (S), T2102.2 (S), T2103.2 (S), T2104.2 (S), T2105.2 (S), T2106.2 (S), T2107.2 (S), T2108.2 (S), T2109.2 (S), T2110.2 (S); also elsewhere on the board
MON_SP_1_FAIL_LED_A: LED2109.A, R2119.2
MON_SP_1_FAIL_LED_C: LED2109.C, T2109.3 (D)
MON_SP_1_TCK_LED_A: LED2101.A, R2103.2
MON_SP_1_TCK_LED_C: LED2101.C, T2101.3 (D)
MON_SP_1_TDI_LED_A1: LED2107.A, R2115.2
MON_SP_1_TDI_LED_C1: LED2107.C, T2107.3 (D)
MON_SP_1_TDO_LED_A1: LED2105.A, R2111.2
MON_SP_1_TDO_LED_C1: LED2105.C, T2105.3 (D)
MON_SP_1_TMS_LED_A1: LED2103.A, R2107.1
MON_SP_1_TMS_LED_C1: LED2103.C, T2103.3 (D)
MON_SP_2_FAIL_LED_A: LED2110.A, R2120.2
MON_SP_2_FAIL_LED_C: LED2110.C, T2110.3 (D)
MON_SP_2_TCK_LED_A1: LED2102.A, R2104.2
MON_SP_2_TCK_LED_C1: LED2102.C, T2102.3 (D)
MON_SP_2_TDI_LED_A2: LED2108.A, R2116.2
MON_SP_2_TDI_LED_C2: LED2108.C, T2108.3 (D)
MON_SP_2_TDO_LED_A2: LED2106.A, R2112.2
MON_SP_2_TDO_LED_C2: LED2106.C, T2106.3 (D)
MON_SP_2_TMS_LED_A2: LED2104.A, R2108.1
MON_SP_2_TMS_LED_C2: LED2104.C, T2104.3 (D)
P3V3: R2103.1, R2104.1, R2107.2, R2108.2, R2111.1, R2112.1, R2115.1, R2116.1, R2119.1, R2120.1; also elsewhere on the board
SP_1_FAIL_FPGA: R2117.2; also elsewhere on the board
SP_1_FAIL_FPGA_G: R2117.1, T2109.1 (G)
SP_1_TCK: R2101.2; also elsewhere on the board
SP_1_TCK_G: R2101.1, T2101.1 (G)
SP_1_TDI_COMP: R2113.2; also elsewhere on the board
SP_1_TDI_COMP_G: R2113.1, T2107.1 (G)
SP_1_TDO: R2109.2; also elsewhere on the board
SP_1_TDO_G: R2109.1, T2105.1 (G)
SP_1_TMS: R2105.2; also elsewhere on the board
SP_1_TMS_G: R2105.1, T2103.1 (G)
SP_2_FAIL_FPGA: R2118.2; also elsewhere on the board
SP_2_FAIL_FPGA_G: R2118.1, T2110.1 (G)
SP_2_TCK: R2102.2; also elsewhere on the board
SP_2_TCK_G: R2102.1, T2102.1 (G)
SP_2_TDI_COMP: R2114.2; also elsewhere on the board
SP_2_TDI_COMP_G: R2114.1, T2108.1 (G)
SP_2_TDO: R2110.2; also elsewhere on the board
SP_2_TDO_G: R2110.1, T2106.1 (G)
SP_2_TMS: R2106.2; also elsewhere on the board
SP_2_TMS_G: R2106.1, T2104.1 (G)

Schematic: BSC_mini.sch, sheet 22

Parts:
LED2201, LED2202: red; S_0805; PART_CODE_BEL LED_PAC_S_0805_VAL_red
R2201, R2202: 100k; S_0805; PART_CODE_BEL R_PAC_S_0805_VAL_100k
R2203, R2204: 2k7; S_0805; PART_CODE_BEL R_PAC_S_0805_VAL_2k7
R2205, R2206: 750; S_0805; PART_CODE_BEL R_PAC_S_0805_VAL_750
T2201, T2202, T2203, T2204: DMG3420U; S_SOT23; PART_CODE_BEL T_PAC_S_SOT23_VAL_DMG3420U

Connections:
GND: T2201.2 (S), T2202.2 (S), T2203.2 (S), T2204.2 (S); also elsewhere on the board
MON_SP_1_TRST_LED_A: LED2201.A, R2205.2
MON_SP_1_TRST_LED_C: LED2201.C, T2203.3 (D)
MON_SP_2_TRST_LED_A: LED2202.A, R2206.2
MON_SP_2_TRST_LED_C: LED2202.C, T2204.3 (D)
P3V3: R2203.1, R2204.1, R2205.1, R2206.1; also elsewhere on the board
SP_1_TRST_N: R2201.1; also elsewhere on the board
SP_1_TRST_N_D: R2203.2, T2201.3 (D), T2203.1 (G)
SP_1_TRST_N_G: R2201.2, T2201.1 (G)
SP_2_TRST_N: R2202.1; also elsewhere on the board
SP_2_TRST_N_D: R2204.2, T2202.3 (D), T2204.1 (G)
SP_2_TRST_N_G: R2202.2, T2202.1 (G)

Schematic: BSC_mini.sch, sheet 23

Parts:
LED2301, LED2302, LED2303, LED2304, LED2305, LED2306, LED2307, LED2308: green; S_0805; PART_CODE_BEL LED_PAC_S_0805_VAL_green
R2301, R2302, R2305, R2306, R2309, R2310, R2313, R2314: 100k; S_0805; PART_CODE_BEL R_PAC_S_0805_VAL_100k
R2303, R2304, R2307, R2308, R2311, R2312, R2315, R2316: 160; S_0805; PART_CODE_BEL R_PAC_S_0805_VAL_160
T2301, T2302, T2303, T2304, T2305, T2306, T2307, T2308: DMG3420U; S_SOT23; PART_CODE_BEL T_PAC_S_SOT23_VAL_DMG3420U

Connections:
GND: T2301.2 (S), T2302.2 (S), T2303.2 (S), T2304.2 (S), T2305.2 (S), T2306.2 (S), T2307.2 (S), T2308.2 (S); also elsewhere on the board
MON_SP_1_DIO_1_ADJ_LED_A: LED2301.A, R2303.2
MON_SP_1_DIO_1_ADJ_LED_C: LED2301.C, T2301.3 (D)
MON_SP_1_DIO_1_P3V3_LED_A: LED2305.A, R2311.2
MON_SP_1_DIO_1_P3V3_LED_C: LED2305.C, T2305.3 (D)
MON_SP_1_DIO_2_ADJ_LED_A: LED2303.A, R2307.2
MON_SP_1_DIO_2_ADJ_LED_C: LED2303.C, T2303.3 (D)
MON_SP_1_DIO_2_P3V3_LED_A: LED2307.A, R2315.2
MON_SP_1_DIO_2_P3V3_LED_C: LED2307.C, T2307.3 (D)
MON_SP_2_DIO_1_ADJ_LED_A: LED2302.A, R2304.2
MON_SP_2_DIO_1_ADJ_LED_C: LED2302.C, T2302.3 (D)
MON_SP_2_DIO_1_P3V3_LED_A: LED2306.A, R2312.2
MON_SP_2_DIO_1_P3V3_LED_C1: LED2306.C, T2306.3 (D)
MON_SP_2_DIO_2_ADJ_LED_A: LED2304.A, R2308.2
MON_SP_2_DIO_2_ADJ_LED_C: LED2304.C, T2304.3 (D)
MON_SP_2_DIO_2_P3V3_LED_A: LED2308.A, R2316.2
MON_SP_2_DIO_2_P3V3_LED_C: LED2308.C, T2308.3 (D)
P3V3: R2303.1, R2304.1, R2307.1, R2308.1, R2311.1, R2312.1, R2315.1, R2316.1; also elsewhere on the board
SP_1_DIO_1_ADJ: R2301.2; also elsewhere on the board
SP_1_DIO_1_ADJ_G: R2301.1, T2301.1 (G)
SP_1_DIO_1_P3V3: R2309.2; also elsewhere on the board
SP_1_DIO_1_P3V3_G: R2309.1, T2305.1 (G)
SP_1_DIO_2_ADJ: R2305.2; also elsewhere on the board
SP_1_DIO_2_ADJ_G: R2305.1, T2303.1 (G)
SP_1_DIO_2_P3V3: R2313.2; also elsewhere on the board
SP_1_DIO_2_P3V3_G: R2313.1, T2307.1 (G)
SP_2_DIO_1_ADJ: R2302.2; also elsewhere on the board
SP_2_DIO_1_ADJ_G: R2302.1, T2302.1 (G)
SP_2_DIO_1_P3V3: R2310.2; also elsewhere on the board
SP_2_DIO_1_P3V3_G: R2310.1, T2306.1 (G)
SP_2_DIO_2_ADJ: R2306.2; also elsewhere on the board
SP_2_DIO_2_ADJ_G: R2306.1, T2304.1 (G)
SP_2_DIO_2_P3V3: R2314.2; also elsewhere on the board
SP_2_DIO_2_P3V3_G: R2314.1, T2308.1 (G)
